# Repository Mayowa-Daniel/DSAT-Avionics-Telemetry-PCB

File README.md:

# DSAT-Avionics-Telemetry-PCB
D.S.A.T Senior Design Project Project

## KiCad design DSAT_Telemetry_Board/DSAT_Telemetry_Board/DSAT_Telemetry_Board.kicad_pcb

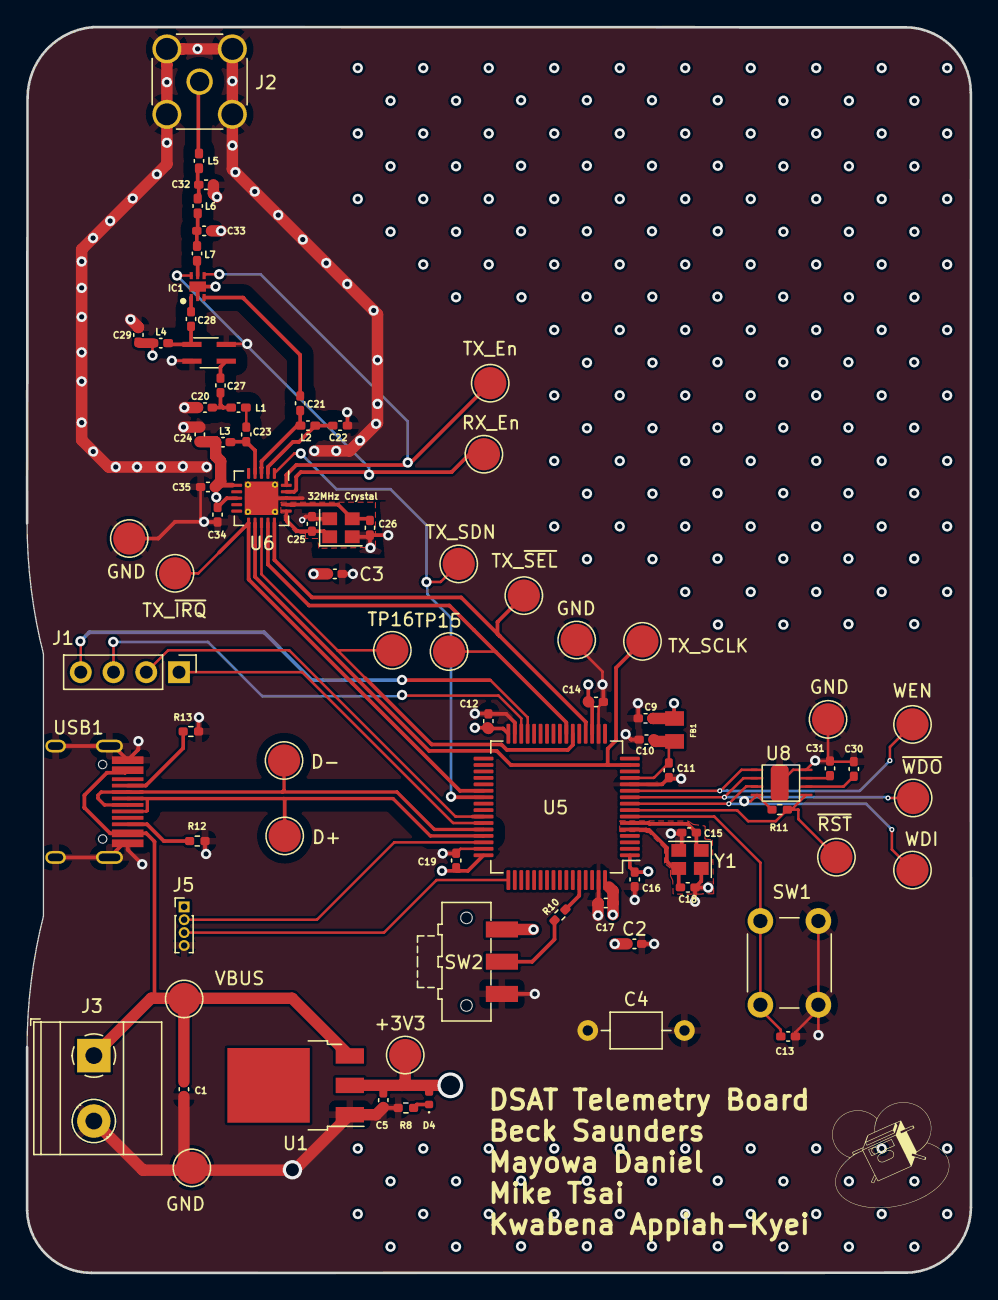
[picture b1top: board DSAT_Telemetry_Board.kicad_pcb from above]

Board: 4 copper layers, 73.2 x 96.6 mm, 79 parts (0 on the bottom side), 49 nets.

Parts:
+3V3: Test_VDD; TestPoint_Pad_D2.5mm
C1, C5: 22uF; C_0402_1005Metric_Pad0.74x0.62mm_HandSolder
C2, C3, C9, C10: 1uF; C_0402_1005Metric_Pad0.74x0.62mm_HandSolder
C4: 100uF; C_Axial_L3.8mm_D2.6mm_P7.50mm_Horizontal
C11, C30, C31: 10nF; C_0402_1005Metric_Pad0.74x0.62mm_HandSolder
C12, C13, C14, C16, C17, C34, C35: 100nF; C_0402_1005Metric_Pad0.74x0.62mm_HandSolder
C15, C18, C32: 10pF; C_0402_1005Metric_Pad0.74x0.62mm_HandSolder
C19: 10uF; C_0402_1005Metric_Pad0.74x0.62mm_HandSolder
C20: 15pF; C_0402_1005Metric_Pad0.74x0.62mm_HandSolder
C21, C22: 4.48pF; C_0402_1005Metric_Pad0.74x0.62mm_HandSolder
C23: 9.2nF; C_0402_1005Metric_Pad0.74x0.62mm_HandSolder
C24, C29: 0.1uF; C_0402_1005Metric_Pad0.74x0.62mm_HandSolder
C25, C26: 20uF; C_0402_1005Metric_Pad0.74x0.62mm_HandSolder
C27: 100pF; C_0402_1005Metric_Pad0.74x0.62mm_HandSolder
C28: 1.5nF; C_0402_1005Metric_Pad0.74x0.62mm_HandSolder
C33: 12pF; C_0402_1005Metric_Pad0.74x0.62mm_HandSolder
D4: LED; LED_0402_1005Metric
D+: Test_USB+; TestPoint_Pad_D2.5mm
D-: Test_USB-; TestPoint_Pad_D2.5mm
FB1: 120R; BEADC2012X105N
GND: Test_Watchdog_GND; TestPoint_Pad_D2.5mm
GND#2: Test_SPI_GND; TestPoint_Pad_D2.5mm
GND#3: Test_RX_TX_GND; TestPoint_Pad_D2.5mm
GND#4: Test_VBUS_gnd; TestPoint_Pad_D2.5mm
IC1: CG2409X3-C2; SON50P150X150X40-7N
J1: Conn_01x04_Female; PinHeader_1x04_P2.54mm_Vertical
J2: Conn_Coaxial; SMA_Amphenol_132134_Vertical
J3: Conn_01x02_Female; TerminalBlock_Phoenix_MKDS-1,5-2-5.08_1x02_P5.08mm_Horizont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
J5: Conn_01x04_Male; PinHeader_1x04_P1.00mm_Vertical
L1: 33nH; L_0402_1005Metric_Pad0.77x0.64mm_HandSolder
L2: 41.9nH; L_0402_1005Metric_Pad0.77x0.64mm_HandSolder
L3: 220nH; L_0402_1005Metric_Pad0.77x0.64mm_HandSolder
L4: 3uH; L_0402_1005Metric_Pad0.77x0.64mm_HandSolder
L5: 22nH; L_0402_1005Metric_Pad0.77x0.64mm_HandSolder
L6: 36nH; L_0402_1005Metric_Pad0.77x0.64mm_HandSolder
L7: 30nH; L_0402_1005Metric_Pad0.77x0.64mm_HandSolder
R8: 1k5; R_0402_1005Metric_Pad0.72x0.64mm_HandSolder
R10: 10kOhm; R_0402_1005Metric_Pad0.72x0.64mm_HandSolder
R11: 100kOhm; R_0402_1005Metric_Pad0.72x0.64mm_HandSolder
R12, R13: 5.1k; R_0402_1005Metric_Pad0.72x0.64mm_HandSolder
RX_En: Test_RX_En; TestPoint_Pad_D2.5mm
SW1: SW_Push; SW_PUSH_6mm_H4.3mm
SW2: SW_SPDT; SW_SPDT_CK-JS102011SAQN
TP15: Test_SDI; TestPoint_Pad_D2.5mm
TP16: Test_SDO; TestPoint_Pad_D2.5mm
TX_En: Test_TX_En; TestPoint_Pad_D2.5mm
TX_SCLK: Test_SCLK; TestPoint_Pad_D2.5mm
TX_SDN: Test_SDN; TestPoint_Pad_D2.5mm
TX_~{IRQ}: Test_~{IRQ}; TestPoint_Pad_D2.5mm
TX_~{SEL}: Test_~{SEL}; TestPoint_Pad_D2.5mm
U1: AZ1084-3.3; TO-252-3_TabPin4
U5: STM32L433RCTx; LQFP-64_10x10mm_P0.5mm
U6: Si4463; QFN-20-1EP_4x4mm_P0.5mm_EP2.6x2.6mm_ThermalVias
U7: PSA4-5043+; SOT-343_SC-70-4_Handsoldering
U8: Watchdog_Timer
USB1: HRO-TYPE-C-31-M-12; HRO-TYPE-C-31-M-12-HandSoldering
VBUS: Test_VBUS; TestPoint_Pad_D2.5mm
WDI: Test_WDI; TestPoint_Pad_D2.5mm
WEN: Test_WEN; TestPoint_Pad_D2.5mm
Y1: 16MHz; Crystal_SMD_2520-4Pin_2.5x2.0mm
Y2: 30MHz; Crystal_SMD_2520-4Pin_2.5x2.0mm

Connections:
+3.3V: +3V3.1, C2.1, C3.1, C4.1, C5.2, C9.1, C12.1, C14.1, C16.1, C17.1, C19.1, C24.2, C29.1, C34.2, C35.2, D4.2 (A), FB1.2, J5.1, L3.2, L4.1, R11.2, SW2.1 (A), U1.2 (VO), U5.1 (VBAT), U5.19 (VDD), U5.32 (VDD), U5.48 (VDDUSB), U5.64 (VDD), U6.6 (VDD), U6.8 (VDD), U8.8 (VDD)
+3.3VA: C10.1, C11.1, FB1.1, U5.13 (VDDA)
/D+: D+.1, U5.45 (PA12), USB1.6 (DP1), USB1.8 (DP2)
/D-: D-.1, U5.44 (PA11), USB1.5 (DN2), USB1.7 (DN1)
/Low Noise Amplifier1/TX_LNA: C28.2, IC1.1 (RF1)
/Microcontroller/Boot0: R10.1, U5.60 (PH3)
/Microcontroller/Clock_In: C18.1, U5.5 (PH0), Y1.3
/Microcontroller/Clock_Out: C15.2, U5.6 (PH1), Y1.1
/Microcontroller/DEBUG_CLK: J5.3, U5.49 (PA14)
/Microcontroller/DEBUG_DIO: J5.2, U5.46 (PA13)
/Microcontroller/I2C1_SCL: J1.2, U5.42 (PA9)
/Microcontroller/I2C1_SDA: J1.1, U5.43 (PA10)
/Microcontroller/I2C2_SCL: J1.4, U5.29 (PB10)
/Microcontroller/I2C2_SDA: J1.3, U5.30 (PB11)
/Microcontroller/NRST: C13.1, SW1.1, U5.7 (NRST)
/RX_En: IC1.6 (VC1), RX_En.1, U6.19 (GPIO2)
/RX_Switch1/Antenna: J2.1 (In), L5.1
/RX_Switch1/RX: C21.1, IC1.3 (RF2)
/TX_En: IC1.4 (VC2), TX_En.1, U6.20 (GPIO3)
/TX_SCLK: TX_SCLK.1, U5.15 (PA1), U6.12 (SCLK)
/TX_SDI: TP15.1, U5.23 (PA7), U6.14 (SDI)
/TX_SDN: TX_SDN.1, U5.39 (PC8), U6.1 (SDN)
/TX_SDO: TP16.1, U5.22 (PA6), U6.13 (SDO)
/TX_~IRQ: TX_~{IRQ}.1, U5.38 (PC7), U6.11 (~IRQ)
/TX_~SEL: TX_~{SEL}.1, U5.20 (PA4), U6.15 (~SEL)
/Transceiver1/TX_Transceiver: C20.2, L1.2
/WDI: U5.9 (PC1), U8.7 (WDI), WDI.1
/WEN: U5.11 (PC3), U8.5 (WEN), WEN.1
/~RST: R11.1, U5.8 (PC0), U8.1 (~RST)
/~WDO: U5.10 (PC2), U8.6 (~WDO)
GND: C1.1, C2.2, C3.2, C4.2, C5.1, C9.2, C10.2, C11.2, C12.2, C13.2, C14.2, C15.1, C16.2, C17.2, C18.2, C19.2, C20.1, C22.2, C24.1, C25.1, C26.2, C29.2, C30.1, C31.1, C32.1, C33.1, C34.1, C35.1, GND.1, GND#2.1, GND#3.1, GND#4.1, IC1.2 (GND_1), IC1.7 (GND_2), J2.2 (Ext), J3.2, J5.4, R8.2, R12.1, R13.2, SW1.2, SW2.3 (C), U1.1 (GND), U5.12 (VSSA), U5.18 (VSS), U5.31 (VSS), U5.47 (VSS), U5.63 (VSS), U6.18 (GND), U6.21 (GND), U7.2 (Gnd), U7.4 (Gnd), U8.4 (VSS), U8.9 (GND), USB1.1 (GND), USB1.12 (GND), USB1.13 (SHIELD), Y1.2, Y1.4, Y2.2, Y2.4
unnamed: C21.2, L2.1, U6.3 (RXn)
unnamed: C22.1, L2.2, U6.2 (RXp)
unnamed: C23.1, L3.1, U6.4 (TX)
unnamed: C23.2, L1.1
unnamed: C25.2, U6.16 (XOUT), Y2.1
unnamed: C26.1, U6.17 (XIN), Y2.3
unnamed: C27.2, U7.3 (RFin)
unnamed: C28.1, L4.2, U7.1 (RFout)
unnamed: C30.2, U8.2 (CPOR)
unnamed: C31.2, U8.3 (CWDT)
unnamed: C32.2, L5.2, L6.1
unnamed: C33.2, L6.2, L7.1
unnamed: D4.1 (K), R8.1
unnamed: IC1.5 (RFC), L7.2
unnamed: R10.2, SW2.2 (B)
unnamed: R12.2, USB1.10 (CC2)
unnamed: R13.1, USB1.4 (CC1)
VBUS: C1.2, J3.1, U1.3 (VI), USB1.2 (VBUS), USB1.11 (VBUS), VBUS.1

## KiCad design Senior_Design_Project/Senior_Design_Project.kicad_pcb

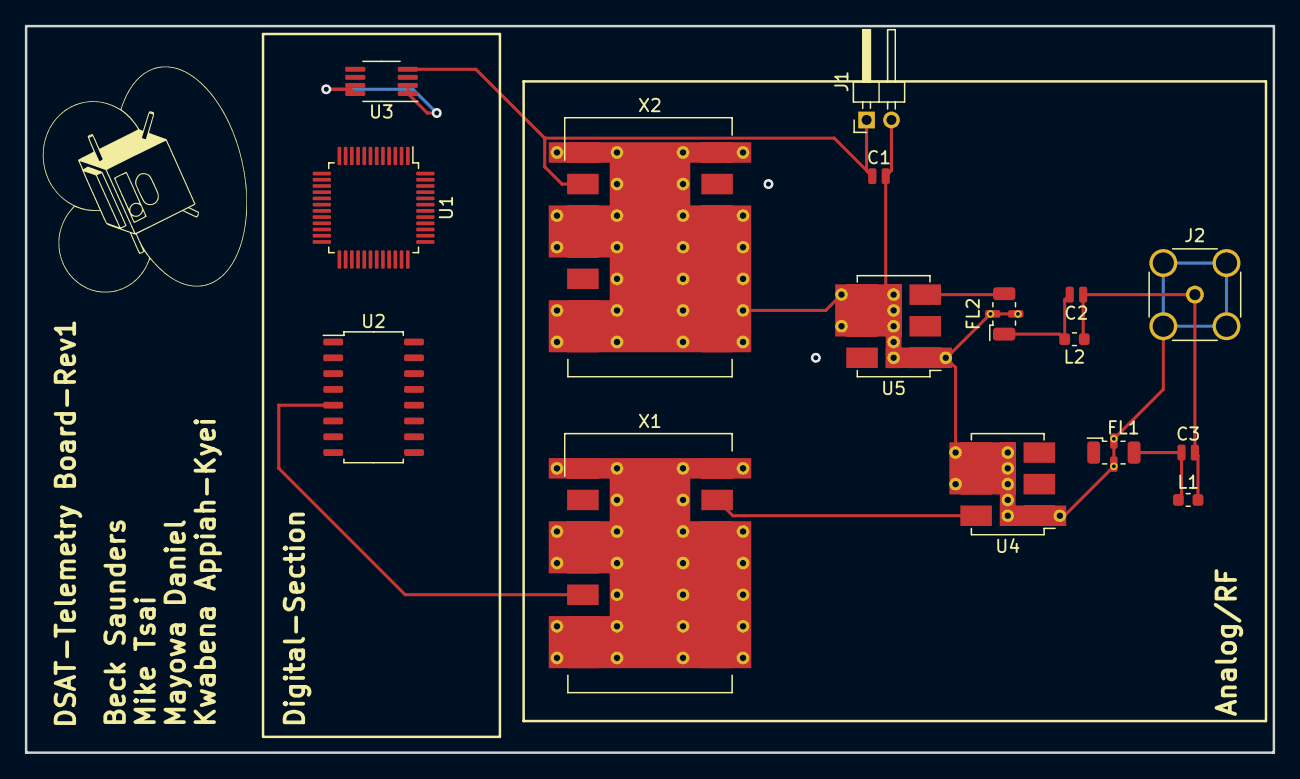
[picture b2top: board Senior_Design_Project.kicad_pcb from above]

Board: 2 copper layers, 100.3 x 58.4 mm, 16 parts (0 on the bottom side), 15 nets.

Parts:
C1, C2, C3: C; C_0504_1310Metric
FL1, FL2: Duplexer; Filter_Mini-Circuits_FV1206
J1: Conn_01x02_Female; PinHeader_1x02_P2.00mm_Horizontal
J2: SMA_Connector; SMA_Amphenol_132134-14_Vertical
L1, L2: L; L_0603_1608Metric
U1: STM32F030C6Tx; LQFP-48_7x7mm_P0.5mm
U2: DAC08; SOIC-16_4.55x10.3mm_P1.27mm
U3: ADC; MSOP-8_3x3mm_P0.65mm
U4, U5: Mixer; Mini-Circuits_CD542_LandPatternPL-052
X1, X2: VCO; Mini-Circuits_BK377_LandPatternPL-005

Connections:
GND: C1.2, FL1.2 (GND), FL1.4 (GND), FL2.2 (GND), FL2.4 (GND), J1.2, J2.2 (Ext), U2.3 (V-), U3.1 (SCL), U3.2 (ALERT), U3.7 (GND), U3.8 (SDA), U4.1 (GND), U4.4 (GND), U4.5 (GND), U5.1 (GND), U5.4 (GND), U5.5 (GND), X1.1 (GND), X1.3 (GND), X1.4 (GND), X1.6 (GND), X1.7 (GND), X1.8 (GND), X1.9 (GND), X1.10 (GND), X1.11 (GND), X1.12 (GND), X1.14 (GND), X2.1 (GND), X2.3 (GND), X2.4 (GND), X2.6 (GND), X2.7 (GND), X2.8 (GND), X2.9 (GND), X2.10 (GND), X2.11 (GND), X2.12 (GND), X2.14 (GND)
unnamed: C2.1, C3.2, J2.1 (In), L1.2, L2.1
unnamed: C3.1, FL1.3 (OUT), L1.1
unnamed: FL1.1 (IN), U4.3 (RF)
unnamed: C2.2, FL2.1 (IN), L2.2
unnamed: FL2.3 (OUT), U5.3 (RF)
unnamed: U1.10 (PA0), U2.15 (R-)
unnamed: U1.37 (PA14), U3.3 (ADR0)
unnamed: U1.38 (PA15), U3.6 (ADR1)
unnamed: U2.5 (B0), X1.5 (Vtune)
unnamed: U2.12 (B7), U2.16 (CMP), X2.5 (Vtune)
unnamed: U3.5 (VA), U5.2 (IF)
unnamed: U2.11 (B6), U4.2 (IF), U4.6 (LO), X1.13 (RFout)
unnamed: U5.6 (LO), X2.13 (RFout)
VCC: C1.1, J1.1, U1.1 (VDD), U2.13 (V+), U3.4 (VIN), X1.2 (VCC), X2.2 (VCC)

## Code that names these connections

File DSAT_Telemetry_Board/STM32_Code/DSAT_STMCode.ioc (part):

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Mcu.Name=STM32L552C(C-E)Tx
Mcu.Package=LQFP48
Mcu.UserName=STM32L552CCTx
PA10.Mode=Asynchronous
PA10.Signal=USART1_RX
PA11.Mode=Device
PA11.Signal=USB_DM
PA12.Mode=Device
PA12.Signal=USB_DP
PA13\ (JTMS/SWDIO).Mode=Serial_Wire
PA13\ (JTMS/SWDIO).Signal=DEBUG_JTMS-SWDIO
PA14\ (JTCK/SWCLK).Mode=Serial_Wire
PA14\ (JTCK/SWCLK).Signal=DEBUG_JTCK-SWCLK
PA3.Signal=GPIO_Analog
PA4.Signal=GPIO_Analog
PA5.Signal=GPIO_Analog
PA6.Signal=GPIO_Analog
PA7.Signal=GPIO_Analog
PA9.Mode=Asynchronous
PA9.Signal=USART1_TX
PB0.Signal=GPIO_Input
PB1.Signal=GPIO_Input
PB10.Signal=GPIO_Output
PB11.Signal=GPIO_Output
PB2.Signal=GPIO_Output
PB6.Mode=I2C
PB6.Signal=I2C1_SCL
PB7.Mode=I2C
PB7.Signal=I2C1_SDA
PH0-OSC_IN\ (PH0).Mode=HSE-External-Oscillator
PH0-OSC_IN\ (PH0).Signal=RCC_OSC_IN
PH1-OSC_OUT\ (PH1).Mode=HSE-External-Oscillator
PH1-OSC_OUT\ (PH1).Signal=RCC_OSC_OUT
RCC.HSE_VALUE=16000000
RCC.SYSCLKFreq_VALUE=32000000
board=custom

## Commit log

2022-11-30 Mockup Board
    Adding KiCad File of mockup Board
2023-01-07 Added New Project Folder "Telemetry Board"
    New KiCad Project with microcontroller configuration design and one transciever.
2023-01-13 Added Hiarchical Sheets
    Placed Modules into hiarchical sheets
    Added Power supply section + Transcievers
    Need to finish conncecting SI transciever chips and the bias tee on the chips + duplexer + LNA
2023-01-14 antenna matching netowrks for Rx and Tx added partially
2023-01-17 change to proper mcu and various schematic changes and additions
2023-01-17 Updated Microcontroller Pinout Names
    Updated Names
2023-01-20 Seperate Branch
    Updated Pin names, Added LNA, Fixed Pins on USB connection
2023-01-25 added Beck edits
2023-02-08 Testing
2023-02-09 Added Watchdog Timer
2023-02-09 Some footprints
2023-02-10 More footprints
2023-02-11 Added Transciever Updates/Biases/RF_Switch
2023-02-11 Trying to fix conflicts
2023-02-15 Added Matching Networks/Linear Regulator/Watchdog Pins
2023-02-17 Added Test Points
2023-02-18 Transceiver sheet - replaced TX_LNA with TX_Transceiver
2023-02-24 RX_SWitch, test points
2023-03-01 Layout halfway done
2023-03-03 Layout changes
2023-03-03 Added Watchdog Timer Footprint
    Added custom footprint for watchdog timer
2023-03-13 Fixed PCB
    Added new voltage regulator, reorganized everything, added new lines, fixed most DRC issues. Added ground and power pours. Added more vias.
2023-03-16 Layout should be doen
2023-03-21 done
2023-03-24 Fixed PCB Errors
    Changed Design rules to allow certain clearance issues, changed keepout zone on STM32 Crystal, changed Footprint of Regulator
